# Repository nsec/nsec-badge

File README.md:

NorthSec 2025 badge
===================

Brought to you by the Team badge of NorthSec.

## Overview

<p align="center">
   <br>
</p>

## Hardware

The NorthSec 2025 badge is loosely based on the ESP32-C3 design with an
[ESP32-C3 microcontroller](https://www.espressif.com/en/products/socs/esp32-c3)
(ESP32-C3-WROOM-02-N4) which is used to drive several periphery devices:

- Eighteen [NeoPixel](https://en.wikipedia.org/wiki/Adafruit_Industries#NeoPixel) RGB LEDs
- Five buttons
- One IR 'pairing' connector
- Two [Shitty Add-On V1.69bis](https://hackaday.com/2019/03/20/introducing-the-shitty-add-on-v1-69bis-standard/) connector

The badge is powered through a USB-C port or through 3 AAA batteries.

If you wish to hack your badge or create a new one based on the hardware. All
the information [is available here](hw/2025/).

## Building the firmware

The firmware is based on the [Espressif IoT Development
Framework](https://docs.platformio.org/en/latest/frameworks/espidf.html). The
build system uses
[PlatformIO](https://docs.platformio.org/en/stable/what-is-platformio.html) to
easily manage the dependencies.

You can install it on Debian / Ubuntu in a python virtualenv with these
commands:

```bash
sudo apt install python3-virtualenv

virtualenv .venv
. .venv/bin/activate

pip install platformio
```

The installation procedure for your OS may differ a little, please consult the
[PlatformIO
documentation](https://docs.platformio.org/en/stable/core/installation/index.html)
if you have any difficulties.

Once the installation is complete you can build the firmware:

```bash
# Conference firmware
pio run -e conference

# CTF firmware
pio run -e ctf
```

## Flashing

Flash the firmware with this command:

```bash
# Conference firmware
pio run -t upload -e conference

# CTF firmware
pio run -t upload -e ctf
```

If multiple badges are connected, you can select which badge will be flash with
the `--upload-port <port_name>` option:

```bash
# Conference firmware
pio run -t upload -e conference --upload-port <port_name>
```

To improve the upload speed, you can skip the build validation/process with the
`-t nobuild` option:

```bash
# Conference firmware
pio run -t upload -t nobuild -e conference
```

## Debugging

To read the logging statements output on the USB serial interface, it is
possible to use `pio device monitor` or `idf.py`'s `monitor` command.

However, you can use your preferred terminal emulator by pointing it to the
`/dev/ttyACM0` device. The badge is configured to output at `115200` bauds,
without parity, and with one stop bit per character.

Note that electrically resetting the board using the hardware switch will cause
the pseudo-terminal device to disappear, making it hard to read the logs
emitted during boot.

Pulsing the DTR signal (lowering it for 1 second) will cause the board to reset
without affecting the pseudo-terminal device, allowing you to read early-boot
messages. This is supported by most terminal emulators.

## Credits
NorthSec CTF badge 2025 is brought to you by the teamwork of:

 - [abdelq](https://github.com/abdelq)
 - [IterateMe](https://github.com/IterateMe)
 - [lle](https://github.com/lle)
 - [nyx0](https://github.com/nyx0)
 - [p0ns](https://github.com/p0ns)
 - [padraignix](https://github.com/padraignix)
 - [Svieg](https://github.com/Svieg)
 - [sylemieux](https://github.com/sylemieux)
 - [TheKGBSpy](https://github.com/TheKGBSpy)
 - [mjeanson](https://github.com/mjeanson)

Special thanks to:
 - [20th](https://github.com/20th)
 - [jgalar](https://github.com/jgalar)

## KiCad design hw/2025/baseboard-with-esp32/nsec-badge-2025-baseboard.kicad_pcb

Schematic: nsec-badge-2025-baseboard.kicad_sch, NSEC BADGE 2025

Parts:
C1, C3, C6, C9: 1uF; C_0603_1608Metric; LCSC C15849
C2, C4, C8: 10uF; C_0805_2012Metric; LCSC C15850
C5: 0.1uF; C_0603_1608Metric; LCSC C14663
C7: 4.7uF; C_0805_2012Metric; LCSC C1779
D1, D2, D3, D5: MBR120LSF; SOD-123_L2.8-W1.8-LS3.7-RD; LCSC C130880
D4: WS2812B; LED_WS2812B_PLCC4_5.0x5.0mm_P3.2mm; LCSC C22461793
J1: Conn_01x15_Socket; PinSocket_1x15_P2.54mm_Vertical; not fitted
J2: Conn_01x08_Socket; PinHeader_1x08_P2.54mm_Vertical; not fitted
J3, J4, J6: Conn_01x02_Socket; PinSocket_1x02_P2.54mm_Vertical; not fitted
J5: Bus_PCI_32bit_Universal; CONN-TH_EH06003-DAW-DF; LCSC C2761459
J7: Conn_01x04_Pin; PinHeader_1x04_P1.27mm_Vertical; not fitted
JP1: SolderJumper_2_Bridged; SolderJumper-2_P1.3mm_Bridged_RoundedPad1.0x1.5mm
JP2: SolderJumper_2_Open; SolderJumper-2_P1.3mm_Open_RoundedPad1.0x1.5mm
KEY1, KEY2: SSSS811101; SW-SMD_SSSS811101; LCSC C109335
LED1, LED2, LED3, LED4: LTST-S220KRKT; LED-SMD_L2.2-W1.0-RD_RED-SIDE; LCSC C284935
R1, R3, R4, R5: 5.1K; R_0603_1608Metric; LCSC C23186
R2, R11: 100K; R_0603_1608Metric; LCSC C25803
R6: 10K; R_0603_1608Metric; LCSC C25804
R7, R8, R9, R12: 1K; R_0603_1608Metric; LCSC C21190
R10: 390K; R_0603_1608Metric; LCSC C23150
U1: ESP32-S3-WROOM-1; LCSC C2913204
U2: AP2112K-3_3TRG1; SOT-25-5_L2.9-W1.6-P0.95-LS2.8-BL; LCSC C51118
U3: TYPE-C-31-M-12; USB-C_SMD-TYPE-C-31-M-12; LCSC C165948
U4: TPSMF05CT1G; SOT-363_L2.0-W1.3-P0.65-LS2.1-BL; LCSC C558443
U5, U6: GT-TC018A-H0375-L1; SW-SMD_L4.7-W3.5-P3.35-EH; LCSC C963235
U7: XDWF-0920-02P; CONN-SMD_XDWF-0920-02P; LCSC C7527581
U8: XT4054K421MR-G; SOT-23-5_L3.0-W1.7-P0.95-LS2.8-BL; LCSC C141405
U9: K2-1102SP-Z4SC-04; KEY-SMD_4P-L6.0-W6.0-P4.50-LS9.0; LCSC C879736

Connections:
+3V3: C2.1, C3.1, C4.1, C5.1, LED2.2 (A), R6.1, U1.2 (3V3), U2.5 (VOUT)
ADC_BATT: R10.2, R11.1, U1.12 (IO8)
BADGE_+3V3: J4.2, J5.A21 (+3.3V), J5.A27 (+3.3V), J5.A33 (+3.3V), J5.A39 (+3.3V), J5.A45 (+3.3V), J5.A53 (+3.3V), J5.B25 (+3.3V), J5.B31 (+3.3V), J5.B36 (+3.3V), J5.B41 (+3.3V), J5.B43 (+3.3V), J5.B54 (+3.3V)
BADGE_RESET: J1.6, J5.B29 (AD[21]), JP2.1 (A)
BADGE_VDD: D4.1 (VDD), J3.2, J5.A5 (+5V), J5.A8 (+5V), J5.A61 (+5V), J5.A62 (+5V), J5.B5 (+5V), J5.B6 (+5V), J5.B61 (+5V), J5.B62 (+5V), KEY2.3
BOOTSEL: U1.27 (IO0), U6.2
BTN_A: J1.5, J5.B30 (AD[19]), U1.23 (IO21)
BTN_DOWN: J1.14, J5.B4 (TDO), U1.7 (IO7)
BTN_TRIGGER: J6.2, U1.6 (IO6), U9.1, U9.2
BTN_UP: J1.15, J5.B2 (TCK), U1.8 (IO15)
CHRG: R9.2, U8.1 (CHRG#)
DOCK_RGB_LED: D4.4 (DIN), U1.25 (IO48)
GND: C1.2, C2.2, C3.2, C4.2, C5.2, C6.2, C7.2, C8.2, C9.2, D4.3 (VSS), J1.1, J3.1, J4.1, J5.A18 (GND), J5.A24 (GND), J5.A30 (GND), J5.A35 (GND), J5.A37 (GND), J5.A42 (GND), J5.A48 (GND), J5.A56 (GND), J5.B3 (GND), J5.B15 (GND), J5.B17 (GND), J5.B22 (GND), J5.B28 (GND), J5.B34 (GND), J5.B38 (GND), J5.B46 (GND), J5.B57 (GND), J6.1, J7.4, KEY1.4, KEY1.5, KEY1.6, KEY1.7, KEY2.4, KEY2.5, KEY2.6, KEY2.7, R1.2, R3.2, R4.2, R5.2, R8.2, R11.2, R12.2, U1.1 (GND), U1.40 (GND), U1.41 (GND), U2.2 (GND), U3.0 (SH), U3.A1 (GND), U3.A12 (GND), U3.B1 (GND), U3.B12 (GND), U4.2, U5.1, U5.3, U5.4, U6.1, U6.3, U6.4, U7.1, U7.3, U7.4, U8.2 (GND), U9.3, U9.4
GPIO1: J1.9, J5.B19 (VIO), U1.19 (IO11)
GPIO2: J1.10, J5.B20 (AD[31]), U1.18 (IO10)
GPIO3: J1.11, J5.B21 (AD[29]), U1.17 (IO9)
I2C_SCL: J1.3, J5.B33 (~C/BE#[2]), U1.5 (IO5)
I2C_SDA: J1.4, J5.B32 (AD[17]), U1.4 (IO4)
IR_IN: J1.13, J5.B7 (~INTB#), U1.22 (IO14)
IR_OUT: J1.12, J5.B8 (~INTD#), U1.21 (IO13)
unnamed: D3.1 (C), KEY2.2
unnamed: D5.1 (C), JP1.2 (B)
unnamed: J7.1, U1.39 (IO1)
unnamed: J7.2, U1.38 (IO2)
unnamed: J7.3, U1.15 (IO3)
unnamed: JP2.2 (B), U1.20 (IO12)
unnamed: LED1.1 (C), R1.1
unnamed: LED2.1 (C), R3.1
unnamed: LED3.1 (C), R9.1
unnamed: LED4.1 (C), R12.1
unnamed: R7.2, R8.1
unnamed: R2.2, U2.3 (EN)
unnamed: R5.1, U3.A5 (CC1)
unnamed: R4.1, U3.B5 (CC2)
POWER_IN: D1.1 (C), D2.1 (C), KEY1.3
RESET: C6.1, R6.2, U1.3 (EN), U5.2
RGB_OUT: J1.2, J5.B60 (~ACK64#)
RPROG: R7.1, U8.5 (PROG)
STAT_LED: LED4.2 (A), U1.26 (IO45)
SV1: J2.1, J5.A3 (TMS), U1.9 (IO16)
SV2: J2.2, J5.A1 (~TRST#), U1.10 (IO17)
SV3: J2.3, J5.A49 (AD[09]), U1.11 (IO18)
SV4: J2.4, J5.A47 (AD[11]), U1.31 (IO38)
SV5: J2.5, J5.A38 (~STOP#), U1.32 (IO39)
SV6: J2.6, J5.A36 (~TRDY#), U1.33 (IO40)
SV7: J2.7, J5.A10 (VIO), U1.34 (IO41)
SV8: J2.8, J5.A9 (RESERVED), U1.35 (IO42)
UART_RX: J1.7, J5.B24 (AD[25]), U1.37 (TXD0)
UART_TX: J1.8, J5.B23 (AD[27]), U1.36 (RXD0)
USB_D+: U1.14 (USB_D+), U3.A6 (DP1), U3.B6 (DP2), U4.6
USB_D-: U1.13 (USB_D-), U3.A7 (DN1), U3.B7 (DN2), U4.5
VBAT: C8.1, C9.1, D1.2 (A), R10.1, U7.2, U8.3 (BAT)
VBUS: D2.2 (A), D5.2 (A), U3.A4 (VBUS), U3.A9 (VBUS), U3.B4 (VBUS), U3.B9 (VBUS), U4.4
VBUS_CHRG: C7.1, JP1.1 (A), LED3.2 (A), U8.4 (VCC)
VDD: C1.1, D3.2 (A), KEY1.2, LED1.2 (A), R2.1, U2.1 (VIN)

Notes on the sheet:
USB
Btn + RGB Led
POWER
ESP32-S3
PCI CONNECTOR
Batt Charger
Breakouts

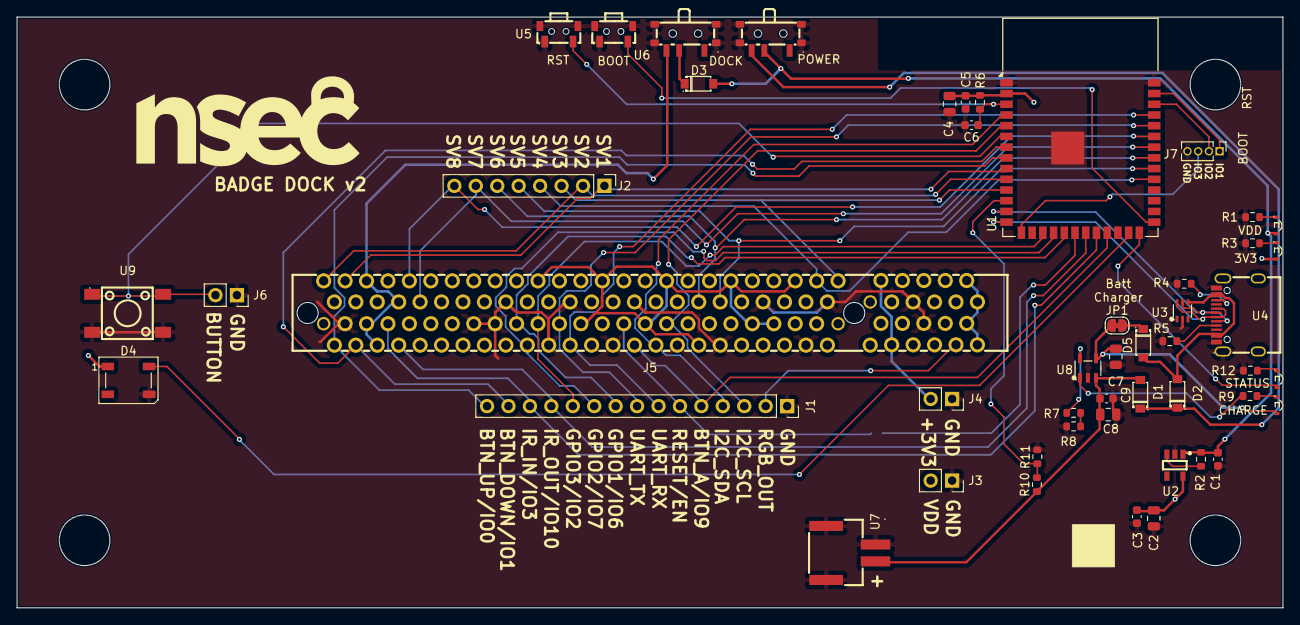
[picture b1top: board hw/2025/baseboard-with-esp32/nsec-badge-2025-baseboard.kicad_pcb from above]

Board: 2 copper layers, 150.0 x 70.0 mm, 50 parts (1 on the bottom side), 55 nets.

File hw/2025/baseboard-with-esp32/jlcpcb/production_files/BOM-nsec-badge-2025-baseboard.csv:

Comment,Designator,Footprint,LCSC,Quantity
SSSS811101,"KEY1,KEY2",SW-SMD_SSSS811101,C109335,2
MBR120LSF,"D1,D2,D3,D5",SOD-123_L2.8-W1.8-LS3.7-RD,C130880,4
XT4054K421MR-G,U8,SOT-23-5_L3.0-W1.7-P0.95-LS2.8-BL,C141405,1
0.1uF,C5,C_0603_1608Metric,C14663,1
1uF,"C1,C3,C6,C9",C_0603_1608Metric,C15849,4
10uF,"C2,C4,C8",C_0805_2012Metric,C15850,3
TYPE-C-31-M-12,U3,USB-C_SMD-TYPE-C-31-M-12,C165948,1
4.7uF,C7,C_0805_2012Metric,C1779,1
1K,"R12,R7,R8,R9",R_0603_1608Metric,C21190,4
WS2812B,D4,LED_WS2812B_PLCC4_5.0x5.0mm_P3.2mm,C22461793,1
390K,R10,R_0603_1608Metric,C23150,1
5.1K,"R1,R3,R4,R5",R_0603_1608Metric,C23186,4
100K,"R11,R2",R_0603_1608Metric,C25803,2
10K,R6,R_0603_1608Metric,C25804,1
Bus_PCI_32bit_Universal,J5,CONN-TH_EH06003-DAW-DF,C2761459,1
LTST-S220KRKT,"LED1,LED2,LED3,LED4",LED-SMD_L2.2-W1.0-RD_RED-SIDE,C284935,4
ESP32-S3-WROOM-1,U1,ESP32-S3-WROOM-1,C2913204,1
AP2112K-3_3TRG1,U2,SOT-25-5_L2.9-W1.6-P0.95-LS2.8-BL,C51118,1
TPSMF05CT1G,U4,SOT-363_L2.0-W1.3-P0.65-LS2.1-BL,C558443,1
XDWF-0920-02P,U7,CONN-SMD_XDWF-0920-02P,C7527581,1
K2-1102SP-Z4SC-04,U9,KEY-SMD_4P-L6.0-W6.0-P4.50-LS9.0,C879736,1
GT-TC018A-H0375-L1,"U5,U6",SW-SMD_L4.7-W3.5-P3.35-EH,C963235,2

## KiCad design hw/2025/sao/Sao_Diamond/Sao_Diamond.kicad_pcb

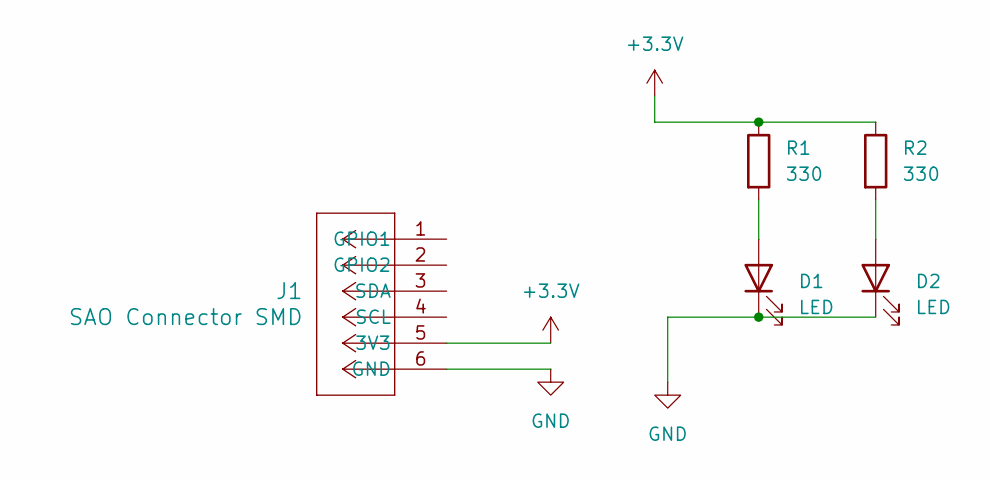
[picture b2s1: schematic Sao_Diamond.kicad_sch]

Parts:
D1, D2: LED; LED_D3.0mm
J1: SAO Connector SMD
R1, R2: 330; R_Axial_DIN0204_L3.6mm_D1.6mm_P7.62mm_Horizontal

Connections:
+3.3V: J1.5 (3V3), R1.1, R2.1
GND: D1.1 (K), D2.1 (K), J1.6 (GND)
unnamed: D1.2 (A), R1.2
unnamed: D2.2 (A), R2.2

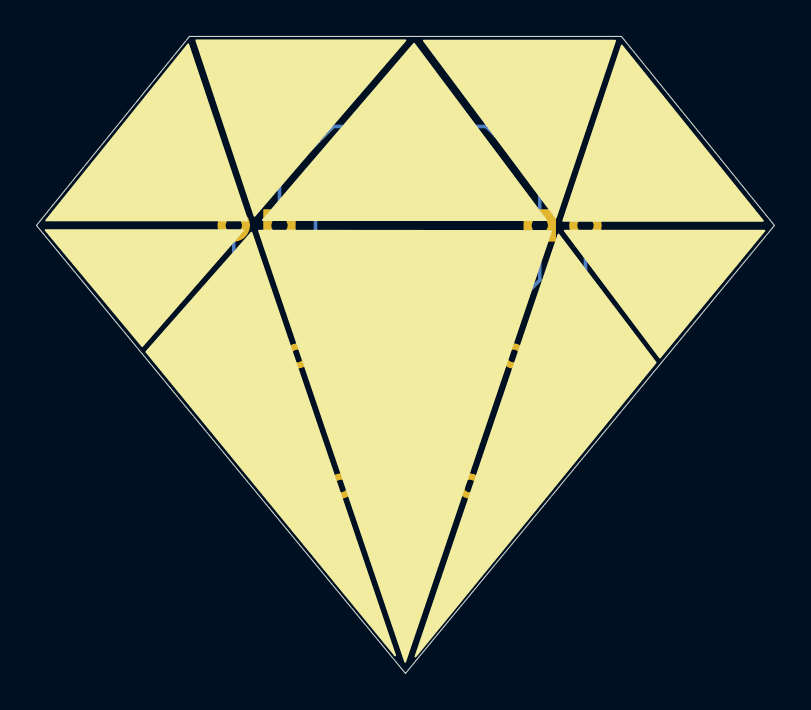
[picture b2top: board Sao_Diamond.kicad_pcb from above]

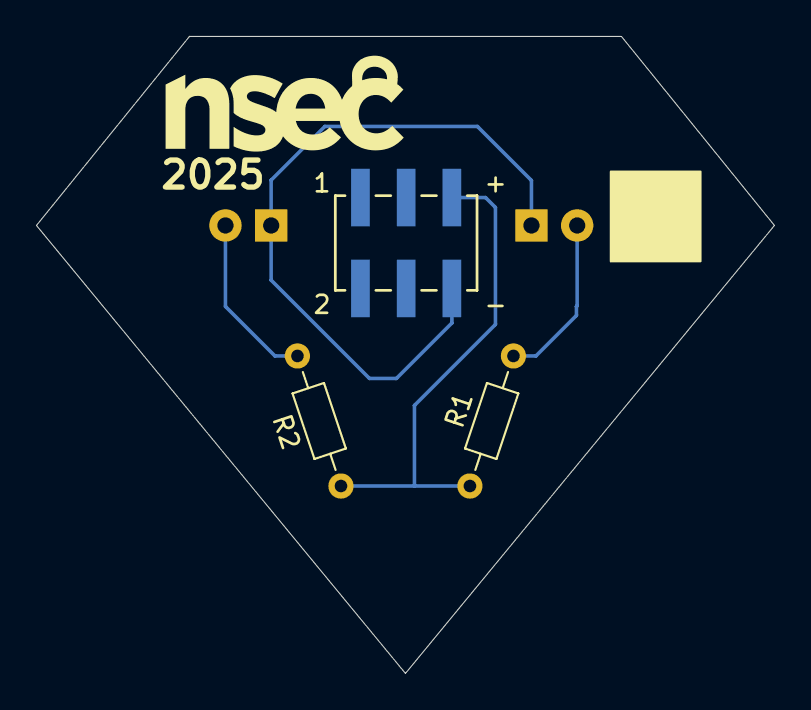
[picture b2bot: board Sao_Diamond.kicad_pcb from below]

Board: 2 copper layers, 41.0 x 35.4 mm, 5 parts (3 on the bottom side), 4 nets.

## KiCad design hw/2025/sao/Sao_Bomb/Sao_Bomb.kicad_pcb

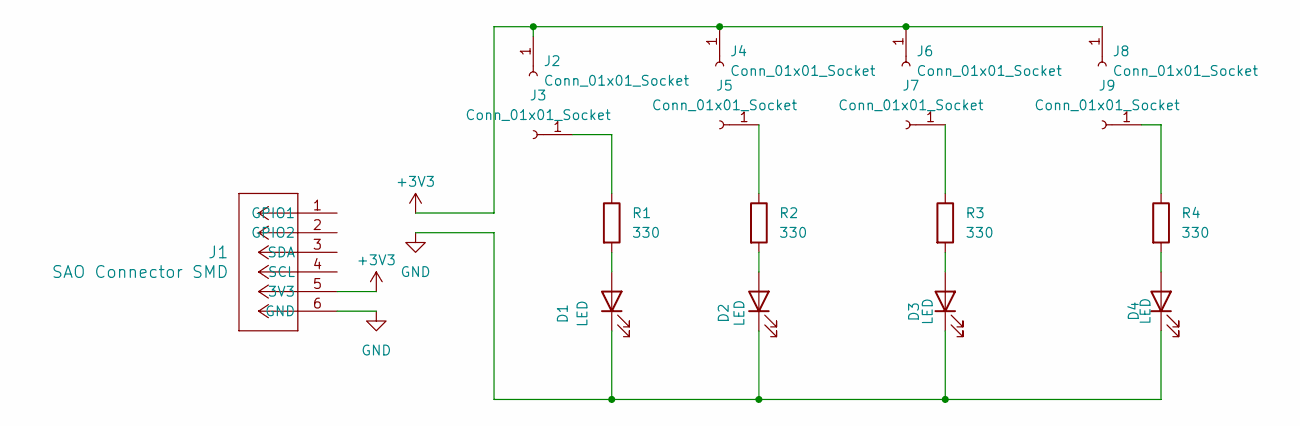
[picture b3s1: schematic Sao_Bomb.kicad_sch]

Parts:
D1, D2, D3, D4: LED; LED_1206_3216Metric_Pad1.42x1.75mm_HandSolder
J1: SAO Connector SMD
J2, J3, J4, J5, J6, J7, J8, J9: Conn_01x01_Socket; PinSocket_1x01_P1.27mm_Vertical
R1, R2, R3, R4: 330; R_1206_3216Metric_Pad1.30x1.75mm_HandSolder

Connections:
+3V3: J1.5 (3V3), J2.1, J4.1, J6.1, J8.1
GND: D1.1 (K), D2.1 (K), D3.1 (K), D4.1 (K), J1.6 (GND)
unnamed: D1.2 (A), R1.2
unnamed: D2.2 (A), R2.2
unnamed: D3.2 (A), R3.2
unnamed: D4.2 (A), R4.2
unnamed: J3.1, R1.1
unnamed: J5.1, R2.1
unnamed: J7.1, R3.1
unnamed: J9.1, R4.1

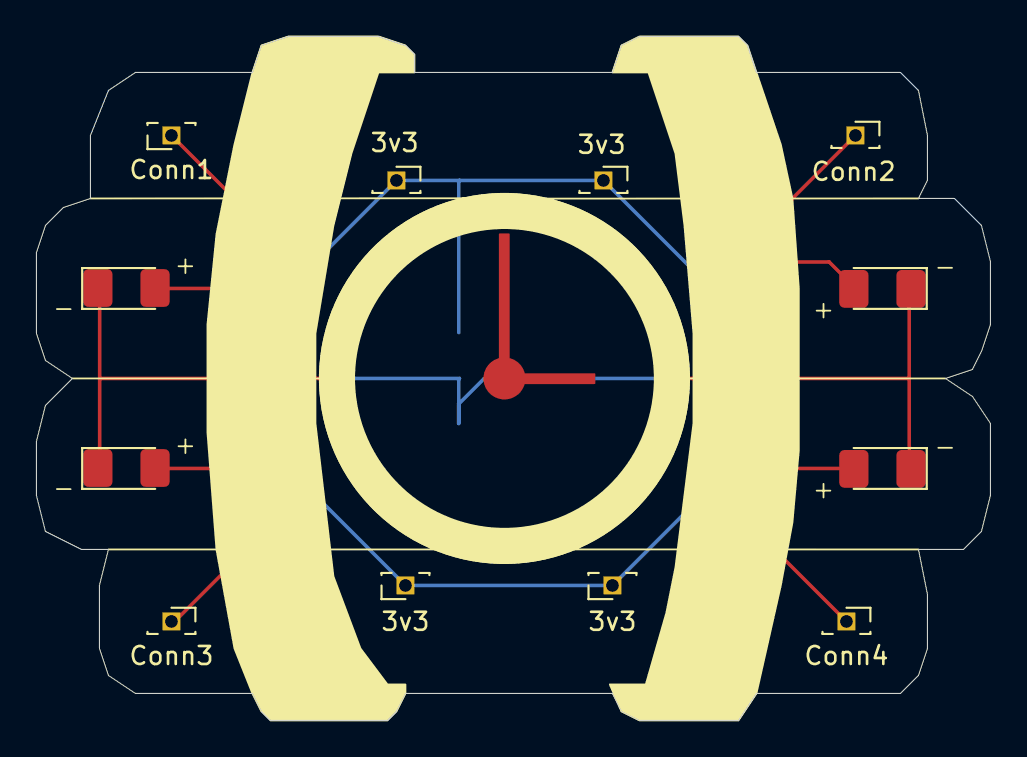
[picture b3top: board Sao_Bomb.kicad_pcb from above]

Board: 2 copper layers, 53.0 x 38.0 mm, 17 parts (1 on the bottom side), 10 nets.

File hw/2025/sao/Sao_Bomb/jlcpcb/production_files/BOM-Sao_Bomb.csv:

Comment,Designator,Footprint,LCSC,Quantity
330,R4,R_1206_3216Metric_Pad1.30x1.75mm_HandSolder,,1
330,R2,R_1206_3216Metric_Pad1.30x1.75mm_HandSolder,,1
330,R3,R_1206_3216Metric_Pad1.30x1.75mm_HandSolder,,1
330,R1,R_1206_3216Metric_Pad1.30x1.75mm_HandSolder,,1
LED,D3,LED_1206_3216Metric_Pad1.42x1.75mm_HandSolder,,1
LED,D4,LED_1206_3216Metric_Pad1.42x1.75mm_HandSolder,,1
LED,D1,LED_1206_3216Metric_Pad1.42x1.75mm_HandSolder,,1
LED,D2,LED_1206_3216Metric_Pad1.42x1.75mm_HandSolder,,1
Conn_01x01_Socket,,PinSocket_1x01_P1.27mm_Vertical,,0
Conn_01x01_Socket,,PinSocket_1x01_P1.27mm_Vertical,,0
Conn_01x01_Socket,,PinSocket_1x01_P1.27mm_Vertical,,0
Conn_01x01_Socket,,PinSocket_1x01_P1.27mm_Vertical,,0
Conn_01x01_Socket,,PinSocket_1x01_P1.27mm_Vertical,,0
Conn_01x01_Socket,,PinSocket_1x01_P1.27mm_Vertical,,0
Conn_01x01_Socket,,PinSocket_1x01_P1.27mm_Vertical,,0
Conn_01x01_Socket,,PinSocket_1x01_P1.27mm_Vertical,,0
SAO Connector SMD,J1,SAO Connector SMD,,1

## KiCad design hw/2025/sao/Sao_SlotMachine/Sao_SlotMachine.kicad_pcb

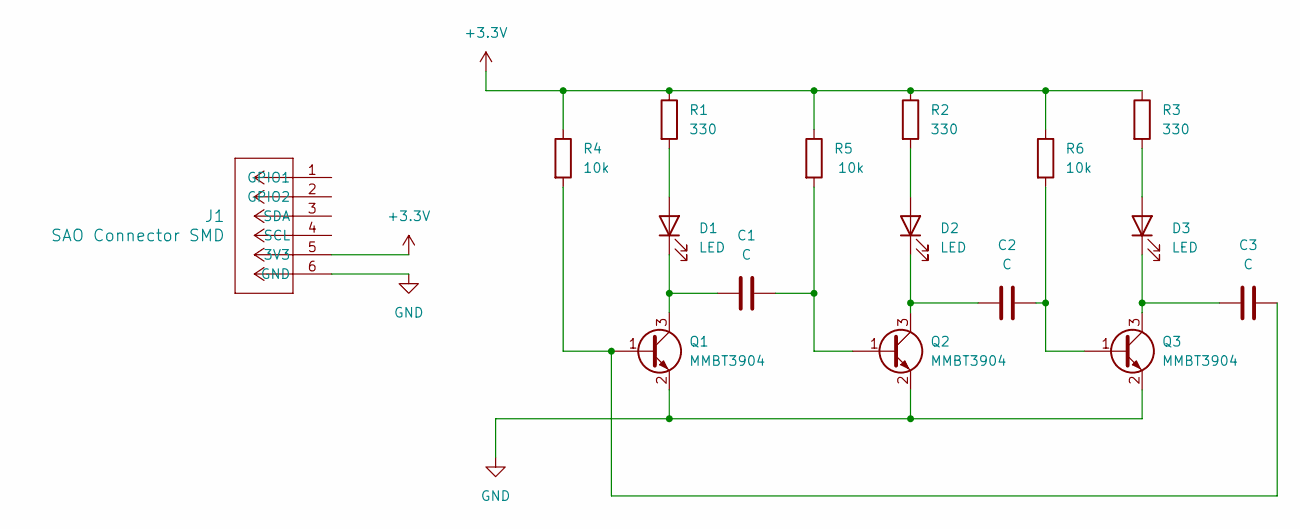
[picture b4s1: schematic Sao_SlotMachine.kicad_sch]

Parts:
C1, C2, C3: C; C_0402_1005Metric_Pad0.74x0.62mm_HandSolder
D1, D2, D3: LED; LED_0402_1005Metric_Pad0.77x0.64mm_HandSolder
J1: SAO Connector SMD
Q1, Q2, Q3: MMBT3904; SOT-23
R1, R2, R3: 330; R_0402_1005Metric_Pad0.72x0.64mm_HandSolder
R4, R5, R6: 10k; R_0402_1005Metric_Pad0.72x0.64mm_HandSolder

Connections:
+3.3V: J1.5 (3V3), R1.1, R2.1, R3.1, R4.1, R5.1, R6.1
GND: J1.6 (GND), Q1.2 (E), Q2.2 (E), Q3.2 (E)
unnamed: D1.2 (A), R1.2
unnamed: C1.1, D1.1 (K), Q1.3 (C)
unnamed: D2.2 (A), R2.2
unnamed: C2.1, D2.1 (K), Q2.3 (C)
unnamed: D3.2 (A), R3.2
unnamed: C3.1, D3.1 (K), Q3.3 (C)
unnamed: C3.2, Q1.1 (B), R4.2
unnamed: C1.2, Q2.1 (B), R5.2
unnamed: C2.2, Q3.1 (B), R6.2

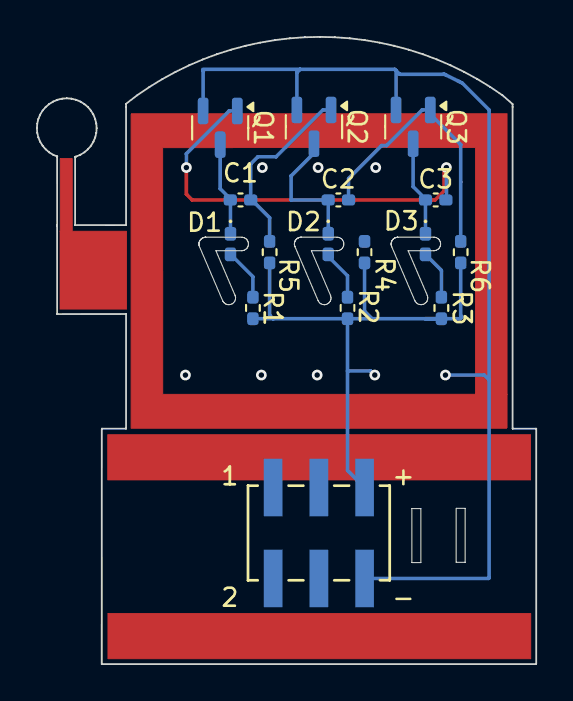
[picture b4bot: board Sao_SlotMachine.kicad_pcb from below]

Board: 2 copper layers, 27.7 x 34.8 mm, 16 parts (16 on the bottom side), 11 nets.

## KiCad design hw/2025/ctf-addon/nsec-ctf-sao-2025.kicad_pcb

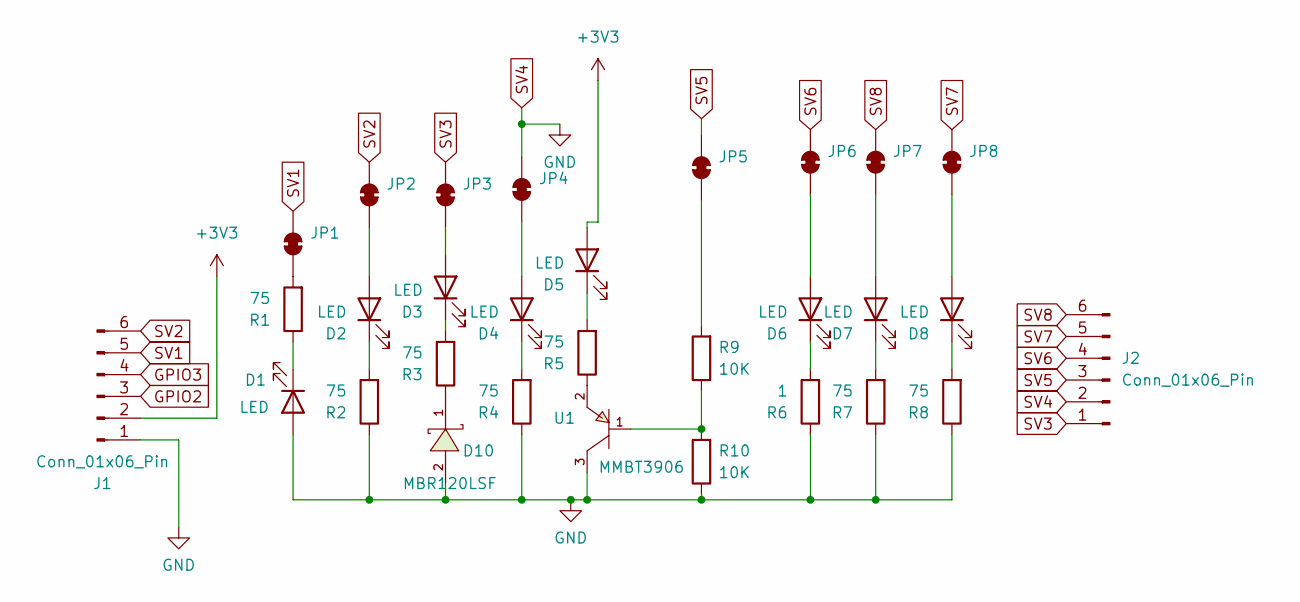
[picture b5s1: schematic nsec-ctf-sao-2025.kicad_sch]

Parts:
D1, D2, D3, D4, D5, D6, D7, D8: LED; LED_1206_3216Metric_Pad1.42x1.75mm_HandSolder; LCSC C965822
D10: MBR120LSF; SOD-123_L2.8-W1.8-LS3.7-RD; LCSC C130880
J1, J2: Conn_01x06_Pin; PinHeader_1x06_P2.54mm_Vertical
JP1, JP2, JP3, JP4, JP5, JP6, JP7, JP8: SolderJumper_2_Bridged; SolderJumper-2_P1.3mm_Bridged_RoundedPad1.0x1.5mm
R1, R2, R3, R4, R5, R7, R8: 75; R_1206_3216Metric_Pad1.30x1.75mm_HandSolder; LCSC C17987
R6: 1; R_1206_3216Metric_Pad1.30x1.75mm_HandSolder; LCSC C1409
R9, R10: 10K; R_0805_2012Metric_Pad1.20x1.40mm_HandSolder; LCSC C17414
U1: MMBT3906; SOT-23-3_L3.0-W1.7-P0.95-LS2.9-BR; LCSC C111114

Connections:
+3V3: D5.2 (A), J1.2
GPIO2: J1.3
GPIO3: J1.4
unnamed: D1.1 (K), R1.1
unnamed: D2.2 (A), JP2.1 (A)
unnamed: D2.1 (K), R2.2
unnamed: D3.2 (A), JP3.1 (A)
unnamed: D3.1 (K), R3.2
unnamed: D4.2 (A), JP4.1 (A)
unnamed: D4.1 (K), R4.2
unnamed: D5.1 (K), R5.2
unnamed: D6.2 (A), JP6.1 (A)
unnamed: D6.1 (K), R6.2
unnamed: D7.2 (A), JP7.1 (A)
unnamed: D7.1 (K), R7.2
unnamed: D8.2 (A), JP8.1 (A)
unnamed: D8.1 (K), R8.2
unnamed: D10.1 (C), R3.1
unnamed: JP1.1 (A), R1.2
unnamed: JP5.1 (A), R9.2
unnamed: R9.1, R10.2, U1.1 (B)
unnamed: R5.1, U1.2 (E)
SV1: J1.5, JP1.2 (B)
SV2: J1.6, JP2.2 (B)
SV3: J2.1, JP3.2 (B)
SV4: D1.2 (A), D10.2 (A), J1.1, J2.2, JP4.2 (B), R2.1, R4.1, R6.1, R7.1, R8.1, R10.1, U1.3 (C)
SV5: J2.3, JP5.2 (B)
SV6: J2.4, JP6.2 (B)
SV7: J2.5, JP8.2 (B)
SV8: J2.6, JP7.2 (B)

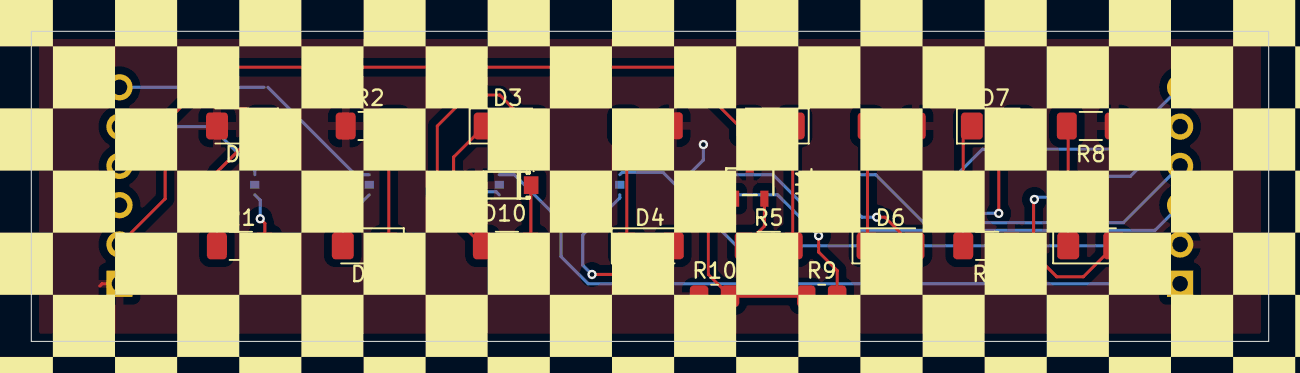
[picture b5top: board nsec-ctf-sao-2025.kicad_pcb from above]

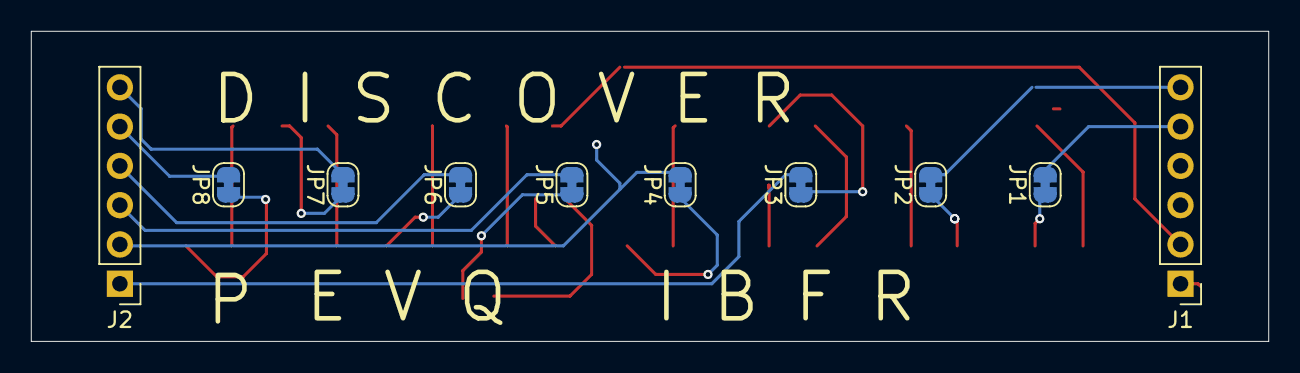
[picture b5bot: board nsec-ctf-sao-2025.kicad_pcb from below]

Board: 2 copper layers, 80.0 x 20.1 mm, 30 parts (10 on the bottom side), 28 nets.

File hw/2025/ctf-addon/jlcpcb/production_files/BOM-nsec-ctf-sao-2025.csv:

Comment,Designator,Footprint,LCSC,Quantity
MMBT3906,U1,SOT-23-3_L3.0-W1.7-P0.95-LS2.9-BR,C111114,1
MBR120LSF,D10,SOD-123_L2.8-W1.8-LS3.7-RD,C130880,1
1,R6,R_1206_3216Metric_Pad1.30x1.75mm_HandSolder,C1409,1
10K,"R10,R9",R_0805_2012Metric_Pad1.20x1.40mm_HandSolder,C17414,2
75,"R1,R2,R3,R4,R5,R7,R8",R_1206_3216Metric_Pad1.30x1.75mm_HandSolder,C17987,7
LED,"D1,D2,D3,D4,D5,D6,D7,D8",LED_1206_3216Metric_Pad1.42x1.75mm_HandSolder,C965822,8

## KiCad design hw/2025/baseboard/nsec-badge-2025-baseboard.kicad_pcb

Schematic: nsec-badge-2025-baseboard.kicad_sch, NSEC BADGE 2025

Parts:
J1: Conn_01x15_Socket; PinSocket_1x15_P2.54mm_Vertical
J2: Conn_01x08_Socket; PinHeader_1x08_P2.54mm_Vertical
J3, J4, J6, J7: Conn_01x02_Socket; PinSocket_1x02_P2.54mm_Vertical
J5: Bus_PCI_32bit_Universal; CONN-TH_EH06003-DAW-DF

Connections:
+3V3: J4.2, J5.A21 (+3.3V), J5.A27 (+3.3V), J5.A33 (+3.3V), J5.A39 (+3.3V), J5.A45 (+3.3V), J5.A53 (+3.3V), J5.B25 (+3.3V), J5.B31 (+3.3V), J5.B36 (+3.3V), J5.B41 (+3.3V), J5.B43 (+3.3V), J5.B54 (+3.3V), J7.2
BTN_A: J1.5, J5.B30 (AD[19])
BTN_DOWN: J1.14, J5.B4 (TDO)
BTN_UP: J1.15, J5.B2 (TCK)
GND: J1.1, J3.1, J4.1, J5.A18 (GND), J5.A24 (GND), J5.A30 (GND), J5.A35 (GND), J5.A37 (GND), J5.A42 (GND), J5.A48 (GND), J5.A56 (GND), J5.B3 (GND), J5.B15 (GND), J5.B17 (GND), J5.B22 (GND), J5.B28 (GND), J5.B34 (GND), J5.B38 (GND), J5.B46 (GND), J5.B57 (GND), J6.1, J7.1
GPIO1: J1.9, J5.B19 (VIO)
GPIO2: J1.10, J5.B20 (AD[31])
GPIO3: J1.11, J5.B21 (AD[29])
I2C_SCL: J1.3, J5.B33 (~C/BE#[2])
I2C_SDA: J1.4, J5.B32 (AD[17])
IR_IN: J1.13, J5.B7 (~INTB#)
IR_OUT: J1.12, J5.B8 (~INTD#)
RESET: J1.6, J5.B29 (AD[21])
RGB_OUT: J1.2, J5.B60 (~ACK64#)
SV1: J2.1, J5.A3 (TMS)
SV2: J2.2, J5.A1 (~TRST#)
SV3: J2.3, J5.A49 (AD[09])
SV4: J2.4, J5.A47 (AD[11])
SV5: J2.5, J5.A38 (~STOP#)
SV6: J2.6, J5.A36 (~TRDY#)
SV7: J2.7, J5.A10 (VIO)
SV8: J2.8, J5.A9 (RESERVED)
UART_RX: J1.7, J5.B24 (AD[25])
UART_TX: J1.8, J5.B23 (AD[27])
VDD: J3.2, J5.A5 (+5V), J5.A8 (+5V), J5.A61 (+5V), J5.A62 (+5V), J5.B5 (+5V), J5.B6 (+5V), J5.B61 (+5V), J5.B62 (+5V), J6.2

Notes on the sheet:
PCI CONNECTOR

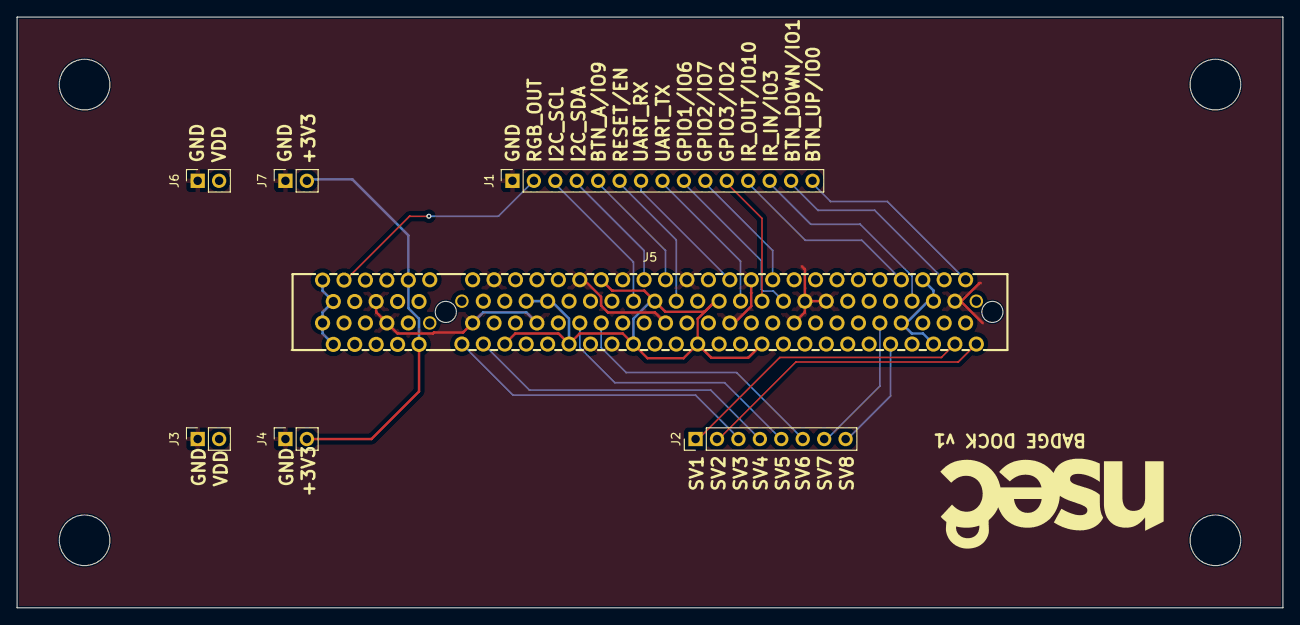
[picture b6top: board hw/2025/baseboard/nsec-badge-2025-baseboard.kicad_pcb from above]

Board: 2 copper layers, 150.0 x 70.0 mm, 7 parts (0 on the bottom side), 25 nets.

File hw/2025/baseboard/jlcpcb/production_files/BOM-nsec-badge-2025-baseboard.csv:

Comment,Designator,Footprint,LCSC,Quantity
Bus_PCI_32bit_Universal,J5,CONN-TH_EH06003-DAW-DF,C2761459,1
Conn_01x02_Socket,,PinSocket_1x02_P2.54mm_Vertical,,0
Conn_01x15_Socket,,PinSocket_1x15_P2.54mm_Vertical,,0
Conn_01x02_Socket,,PinSocket_1x02_P2.54mm_Vertical,,0
Conn_01x02_Socket,,PinSocket_1x02_P2.54mm_Vertical,,0
Conn_01x08_Socket,,PinHeader_1x08_P2.54mm_Vertical,,0
Conn_01x02_Socket,,PinSocket_1x02_P2.54mm_Vertical,,0

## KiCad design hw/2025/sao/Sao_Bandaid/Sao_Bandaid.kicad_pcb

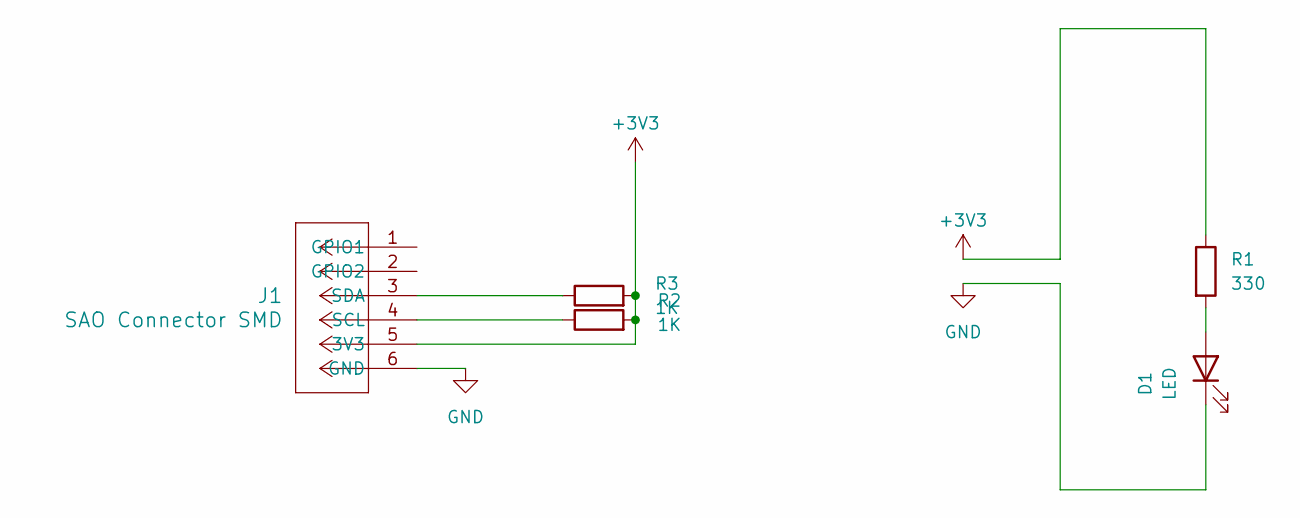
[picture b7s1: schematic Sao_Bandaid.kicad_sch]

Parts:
D1: LED; LED_1206_3216Metric_Pad1.42x1.75mm_HandSolder
J1: SAO Connector SMD
R1: 330; R_1206_3216Metric_Pad1.30x1.75mm_HandSolder
R2, R3: 1K; R_1206_3216Metric_Pad1.30x1.75mm_HandSolder

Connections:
+3V3: J1.5 (3V3), R1.1, R2.2, R3.2
GND: D1.1 (K), J1.6 (GND)
unnamed: D1.2 (A), R1.2
unnamed: J1.4 (SCL), R2.1
unnamed: J1.3 (SDA), R3.1

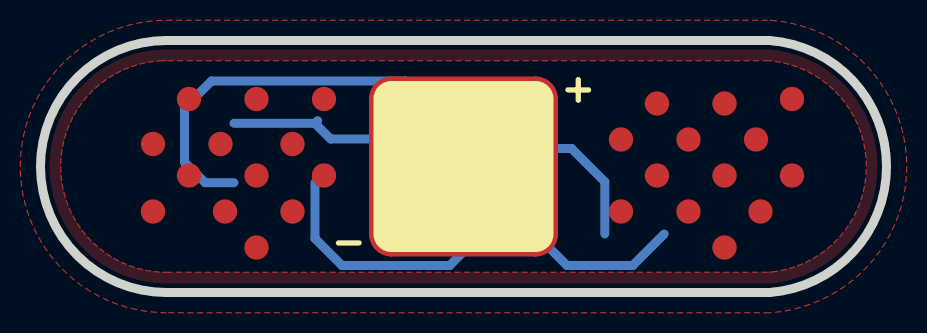
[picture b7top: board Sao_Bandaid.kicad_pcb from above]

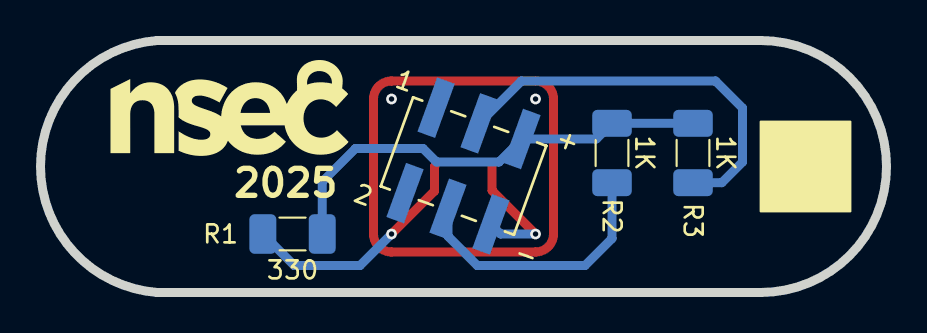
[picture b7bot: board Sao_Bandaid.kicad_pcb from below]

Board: 2 copper layers, 47.0 x 14.0 mm, 5 parts (4 on the bottom side), 5 nets.

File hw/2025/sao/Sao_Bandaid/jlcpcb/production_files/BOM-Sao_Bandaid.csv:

Comment,Designator,Footprint,LCSC,Quantity
SAO Connector SMD,J1,SAO Connector SMD,,1
1K,R3,R_1206_3216Metric_Pad1.30x1.75mm_HandSolder,,1
1K,R2,R_1206_3216Metric_Pad1.30x1.75mm_HandSolder,,1
330,R1,R_1206_3216Metric_Pad1.30x1.75mm_HandSolder,,1
LED,D1,LED_1206_3216Metric_Pad1.42x1.75mm_HandSolder,,1

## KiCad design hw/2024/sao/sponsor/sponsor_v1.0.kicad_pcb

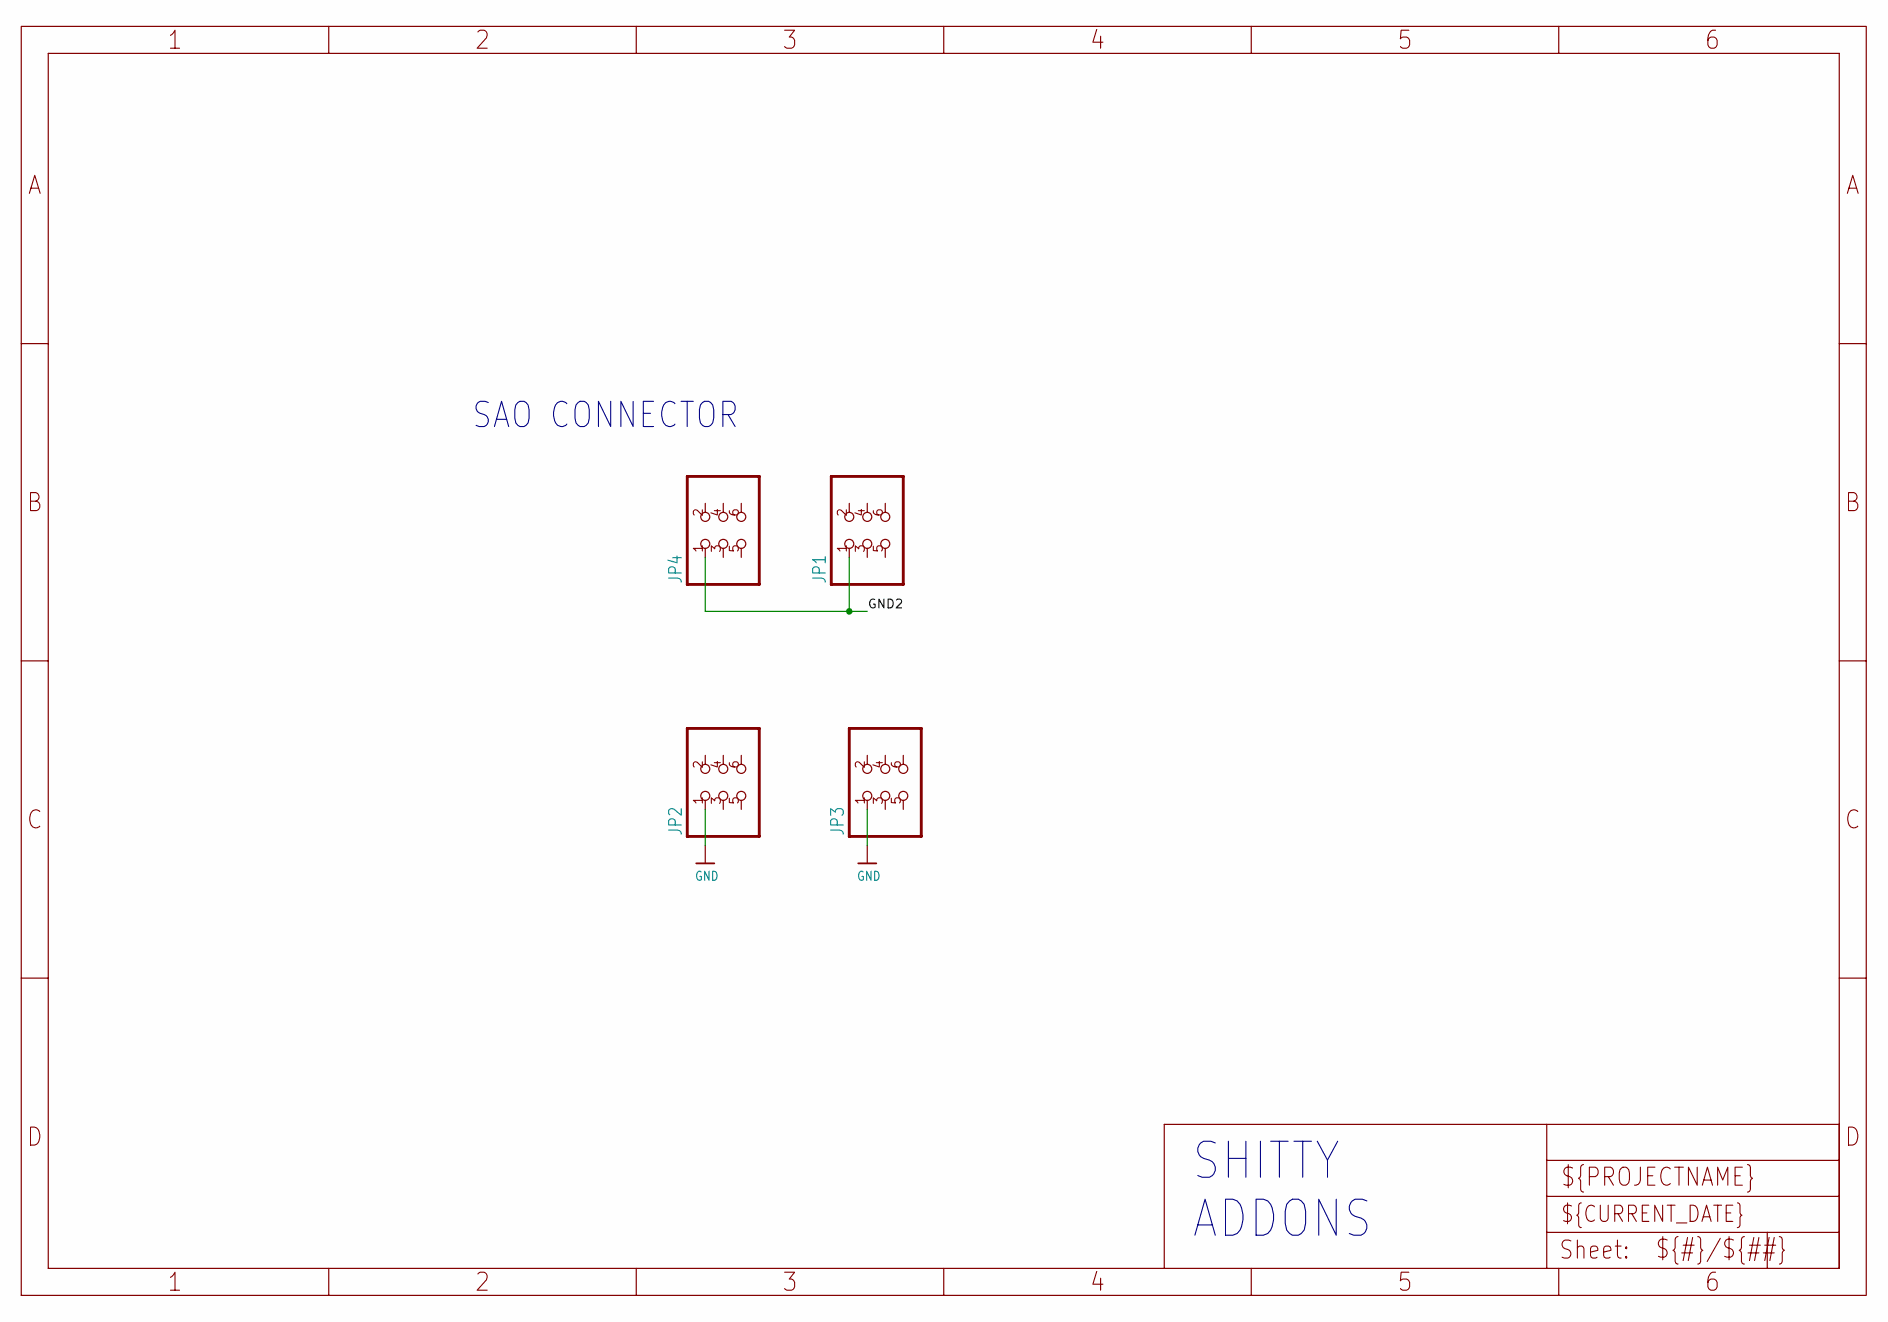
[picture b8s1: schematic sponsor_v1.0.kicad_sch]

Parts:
JP1, JP2, JP3, JP4: PINHD-2X3; 2X03

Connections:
GND: JP2.1, JP3.1
GND2: JP1.1, JP4.1

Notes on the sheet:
SHITTY ADDONS
SAO CONNECTOR

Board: 2 copper layers, 4 parts (0 on the bottom side), 2 nets, no tracks yet.
